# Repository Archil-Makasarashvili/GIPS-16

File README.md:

# GIPS-16
GIPS-16-1 Soviet  plasma display controller

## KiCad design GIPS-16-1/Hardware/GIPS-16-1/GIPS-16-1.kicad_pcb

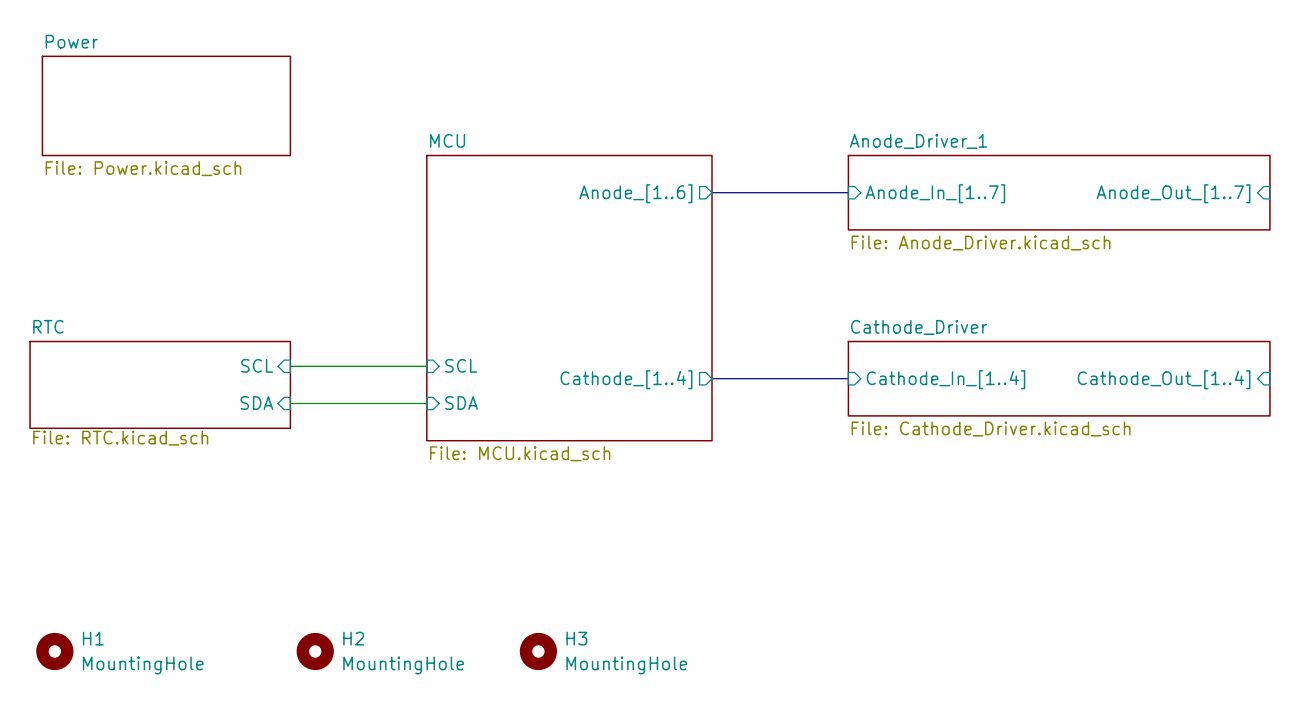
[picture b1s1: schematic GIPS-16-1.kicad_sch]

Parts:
H1, H2, H3: MountingHole; MountingHole_3.2mm_M3

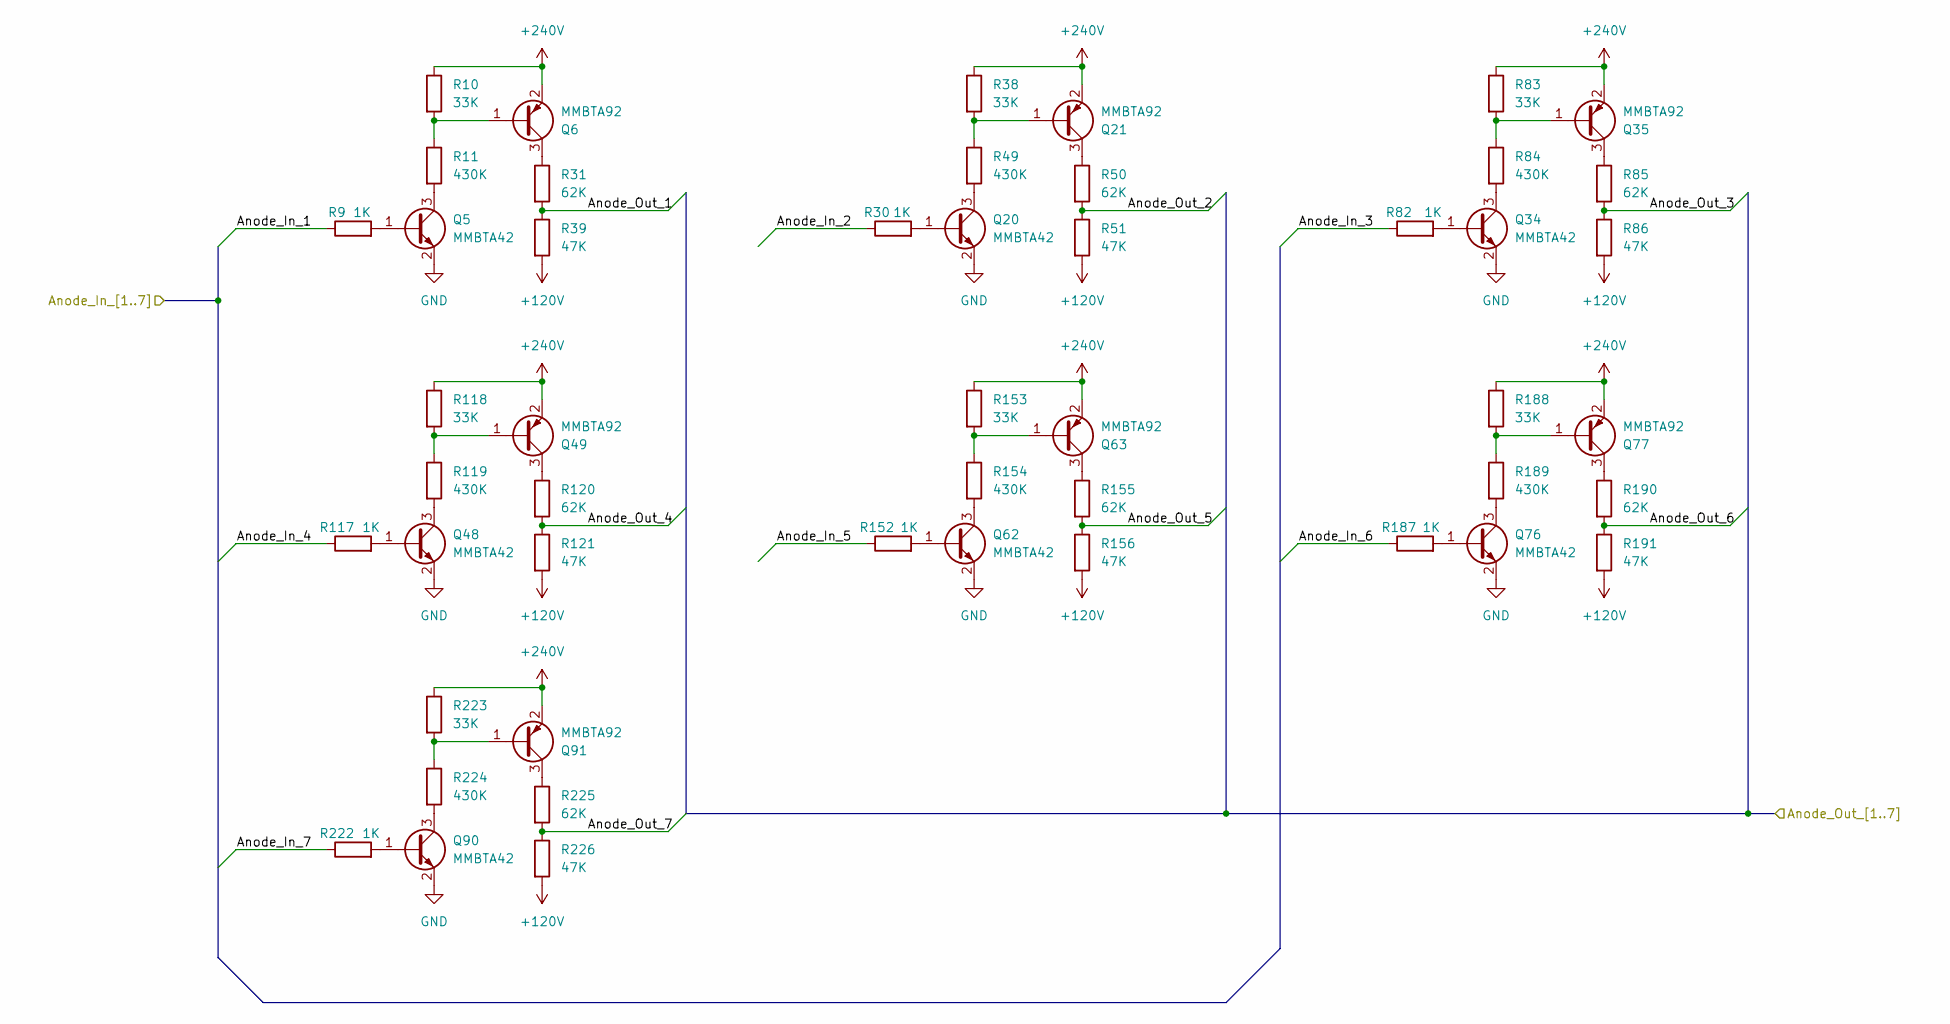
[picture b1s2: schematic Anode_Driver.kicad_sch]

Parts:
Q5, Q20, Q34, Q48, Q62, Q76, Q90: MMBTA42; SOT-23
Q6, Q21, Q35, Q49, Q63, Q77, Q91: MMBTA92; SOT-23
R9, R30, R82, R117, R152, R187, R222: 1K; R_0805_2012Metric_Pad1.20x1.40mm_HandSolder
R10, R38, R83, R118, R153, R188, R223: 33K; R_1206_3216Metric_Pad1.30x1.75mm_HandSolder
R11, R49, R84, R119, R154, R189, R224: 430K; R_1206_3216Metric_Pad1.30x1.75mm_HandSolder
R31, R50, R85, R120, R155, R190, R225: 62K; R_1206_3216Metric_Pad1.30x1.75mm_HandSolder
R39, R51, R86, R121, R156, R191, R226: 47K; R_1206_3216Metric_Pad1.30x1.75mm_HandSolder

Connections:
+120V: R39.2, R51.2, R86.2, R121.2, R156.2, R191.2, R226.2; also elsewhere on the board
+240V: Q6.2 (E), Q21.2 (E), Q35.2 (E), Q49.2 (E), Q63.2 (E), Q77.2 (E), Q91.2 (E), R10.1, R38.1, R83.1, R118.1, R153.1, R188.1, R223.1; also elsewhere on the board
/Anode_Driver_1/Anode_In_1: R9.1; also elsewhere on the board
/Anode_Driver_1/Anode_In_2: R30.1; also elsewhere on the board
/Anode_Driver_1/Anode_In_3: R82.1; also elsewhere on the board
/Anode_Driver_1/Anode_In_4: R117.1; also elsewhere on the board
/Anode_Driver_1/Anode_In_5: R152.1; also elsewhere on the board
/Anode_Driver_1/Anode_In_6: R187.1; also elsewhere on the board
/Anode_Driver_1/Anode_In_7: R222.1
/Anode_Driver_1/Anode_Out_1: R31.2, R39.1
/Anode_Driver_1/Anode_Out_2: R50.2, R51.1
/Anode_Driver_1/Anode_Out_3: R85.2, R86.1
/Anode_Driver_1/Anode_Out_4: R120.2, R121.1
/Anode_Driver_1/Anode_Out_5: R155.2, R156.1
/Anode_Driver_1/Anode_Out_6: R190.2, R191.1
/Anode_Driver_1/Anode_Out_7: R225.2, R226.1
GND: Q5.2 (E), Q20.2 (E), Q34.2 (E), Q48.2 (E), Q62.2 (E), Q76.2 (E), Q90.2 (E); also elsewhere on the board
unnamed: Q5.1 (B), R9.2
unnamed: Q5.3 (C), R11.2
unnamed: Q6.1 (B), R10.2, R11.1
unnamed: Q6.3 (C), R31.1
unnamed: Q20.1 (B), R30.2
unnamed: Q20.3 (C), R49.2
unnamed: Q21.1 (B), R38.2, R49.1
unnamed: Q21.3 (C), R50.1
unnamed: Q34.1 (B), R82.2
unnamed: Q34.3 (C), R84.2
unnamed: Q35.1 (B), R83.2, R84.1
unnamed: Q35.3 (C), R85.1
unnamed: Q48.1 (B), R117.2
unnamed: Q48.3 (C), R119.2
unnamed: Q49.1 (B), R118.2, R119.1
unnamed: Q49.3 (C), R120.1
unnamed: Q62.1 (B), R152.2
unnamed: Q62.3 (C), R154.2
unnamed: Q63.1 (B), R153.2, R154.1
unnamed: Q63.3 (C), R155.1
unnamed: Q76.1 (B), R187.2
unnamed: Q76.3 (C), R189.2
unnamed: Q77.1 (B), R188.2, R189.1
unnamed: Q77.3 (C), R190.1
unnamed: Q90.1 (B), R222.2
unnamed: Q90.3 (C), R224.2
unnamed: Q91.1 (B), R223.2, R224.1
unnamed: Q91.3 (C), R225.1

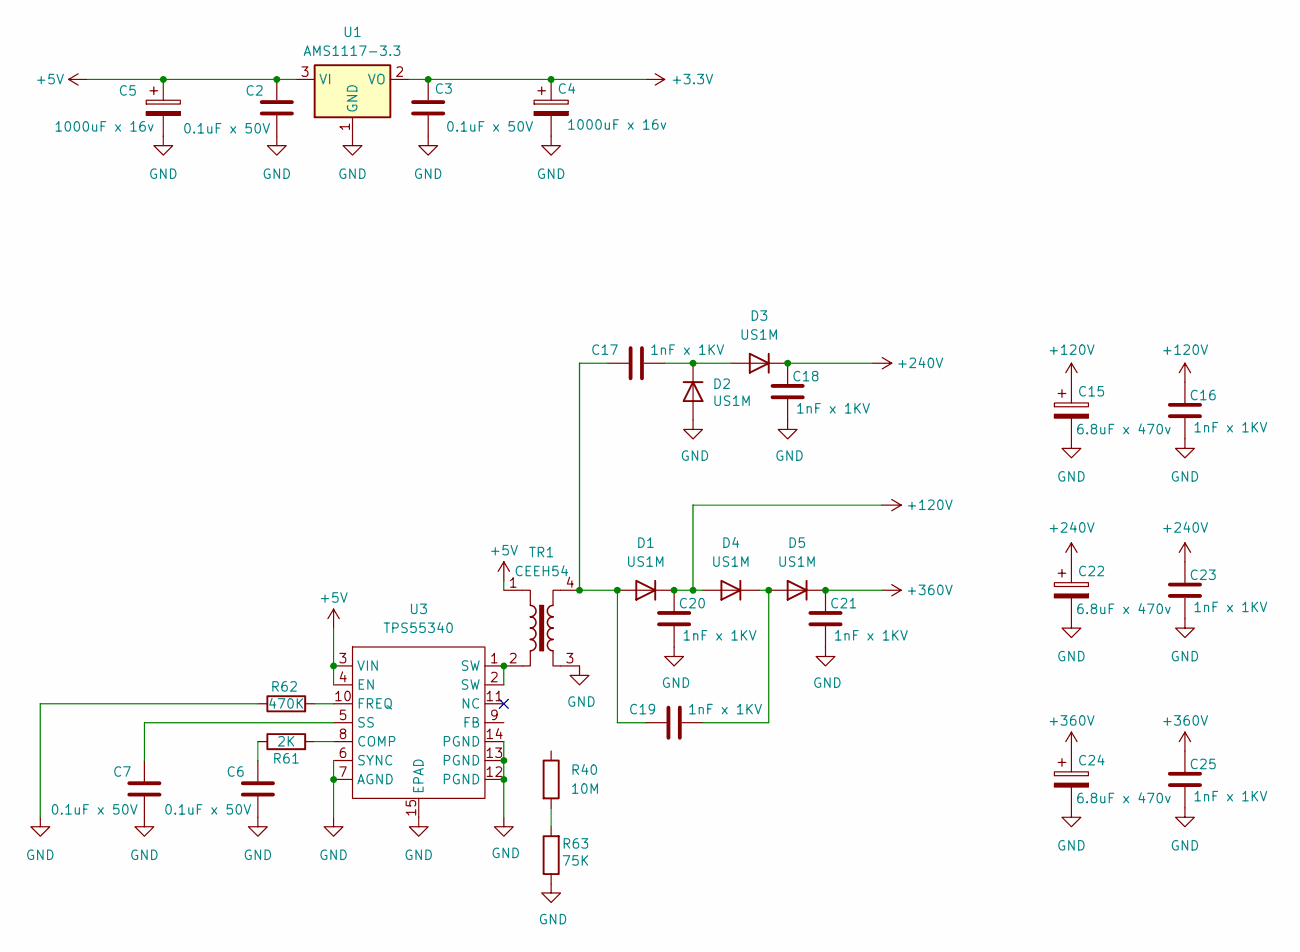
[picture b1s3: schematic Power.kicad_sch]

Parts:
C2, C3, C6, C7: 0.1uF x 50V; C_0805_2012Metric_Pad1.18x1.45mm_HandSolder
C4, C5: 1000uF x 16v; CP_Elec_10x10.5
C15, C22, C24: 6.8uF x 470v; CP_Elec_10x10.5
C16, C23, C25: 1nF x 1KV; C_2220_5750Metric_Pad1.97x5.40mm_HandSolder
C17, C18, C19, C20, C21: 1nF x 1KV; C_Disc_D10.0mm_W2.5mm_P5.00mm
D1, D2, D3, D4, D5: US1M; D_SMA
R40: 10M; R_1206_3216Metric_Pad1.30x1.75mm_HandSolder
R61: 2K; R_0805_2012Metric_Pad1.20x1.40mm_HandSolder
R62: 470K; R_0805_2012Metric_Pad1.20x1.40mm_HandSolder
R63: 75K; R_0805_2012Metric_Pad1.20x1.40mm_HandSolder
TR1: CEEH54; Pulse_P0926NL
U1: AMS1117-3.3; SOT-223-3_TabPin2
U3: TPS55340; TSSOP-14-1EP_4.4x5mm_P0.65mm

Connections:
+3.3V: C3.1, C4.1, U1.2 (VO); also elsewhere on the board
+5V: C2.1, C5.1, TR1.1, U1.3 (VI), U3.3 (VIN), U3.4 (EN); also elsewhere on the board
+120V: C15.1, C16.1, C20.1, D1.1 (K), D4.2 (A); also elsewhere on the board
+240V: C18.1, C22.1, C23.1, D3.1 (K); also elsewhere on the board
+360V: C21.1, C24.1, C25.1, D5.1 (K)
GND: C2.2, C3.2, C4.2, C5.2, C6.2, C7.2, C15.2, C16.2, C18.2, C20.2, C21.2, C22.2, C23.2, C24.2, C25.2, D2.2 (A), R62.1, R63.1, TR1.3, U1.1 (GND), U3.6 (SYNC), U3.7 (AGND), U3.12 (PGND), U3.13 (PGND), U3.14 (PGND), U3.15 (EPAD); also elsewhere on the board
unnamed: C6.1, R61.1
unnamed: C17.1, C19.1, D1.2 (A), TR1.4
unnamed: C17.2, D2.1 (K), D3.2 (A)
unnamed: C19.2, D4.1 (K), D5.2 (A)
unnamed: R40.2, R63.2
unnamed: TR1.2, U3.1 (SW), U3.2 (SW)
unnamed: R61.2, U3.8 (COMP)
unnamed: R62.2, U3.10 (FREQ)
unnamed: C7.1, U3.5 (SS)

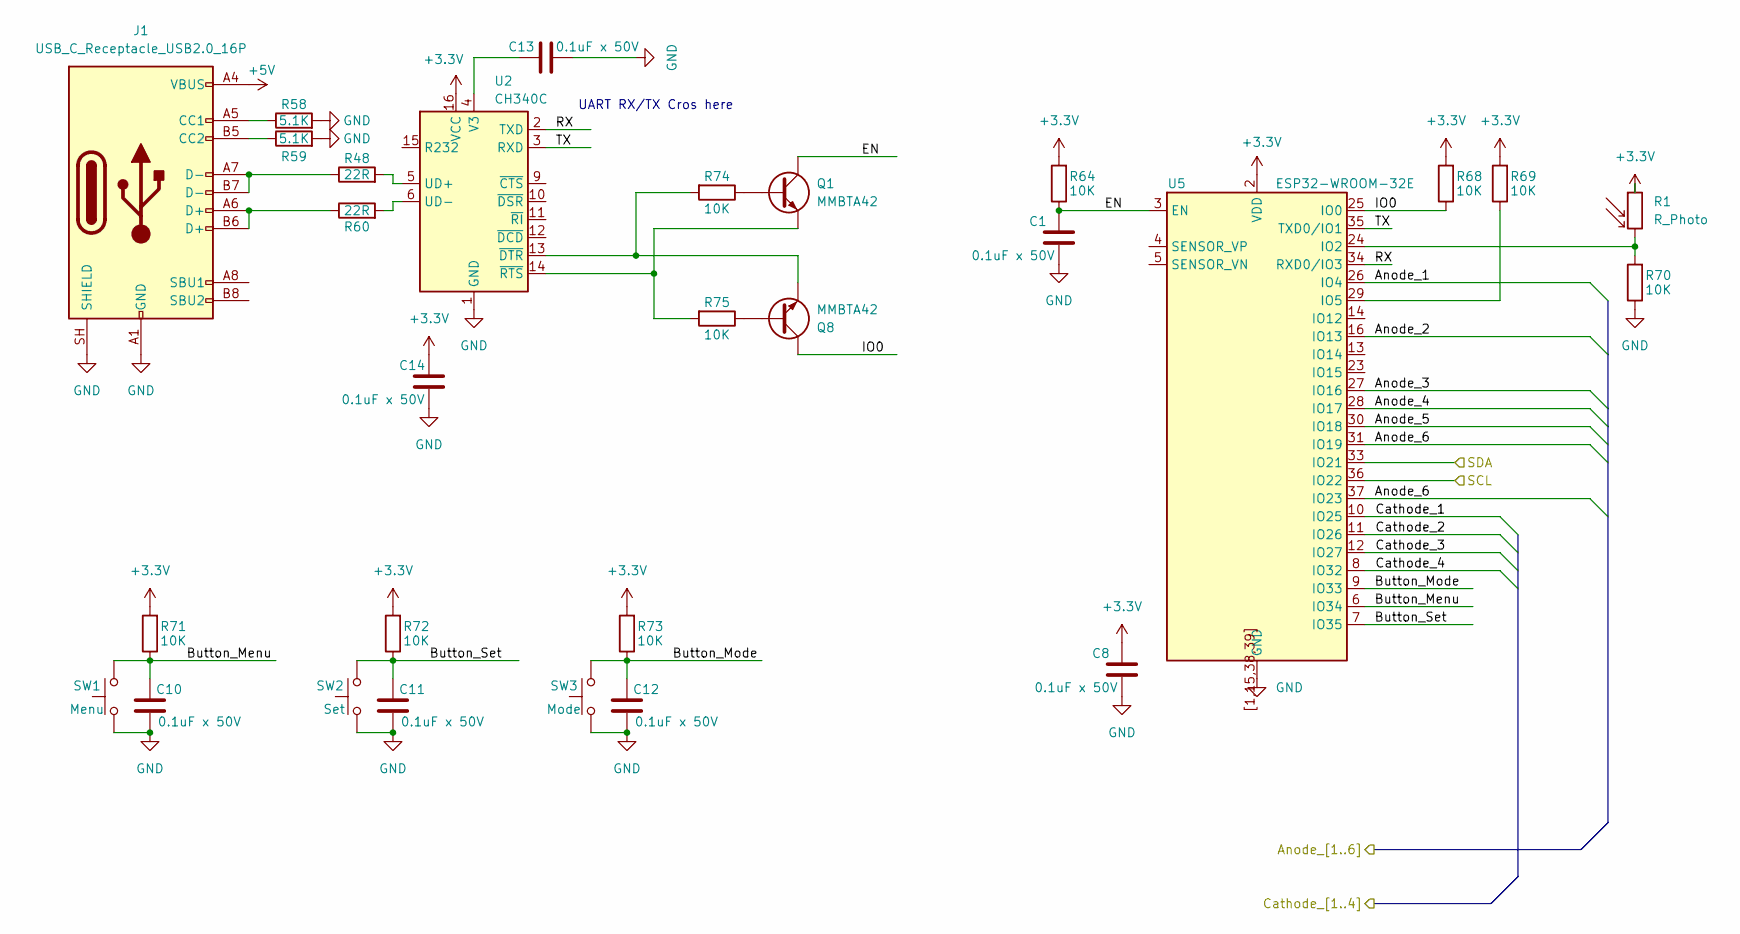
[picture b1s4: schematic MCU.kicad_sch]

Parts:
C1, C8, C10, C11, C12, C13, C14: 0.1uF x 50V; C_0805_2012Metric_Pad1.18x1.45mm_HandSolder
J1: USB_C_Receptacle_USB2.0_16P; USB_C_Receptacle_G-Switch_GT-USB-7010ASV
Q1, Q8: MMBTA42; SOT-23
R1: R_Photo; R_LDR_5.1x4.3mm_P3.4mm_Vertical
R48, R60: 22R; R_0805_2012Metric_Pad1.20x1.40mm_HandSolder
R58, R59: 5.1K; R_0805_2012Metric_Pad1.20x1.40mm_HandSolder
R64, R68, R69, R70, R71, R72, R73, R74, R75: 10K; R_0805_2012Metric_Pad1.20x1.40mm_HandSolder
SW1: Menu; SW_PUSH_6mm_H5mm
SW2: Set; SW_PUSH_6mm_H5mm
SW3: Mode; SW_PUSH_6mm_H5mm
U2: CH340C; SOIC-16_3.9x9.9mm_P1.27mm
U5: ESP32-WROOM-32E

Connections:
+3.3V: C8.1, C14.1, R1.1, R64.2, R68.2, R69.2, R71.2, R72.2, R73.2, U2.16 (VCC), U5.2 (VDD); also elsewhere on the board
+5V: J1.A4 (VBUS), J1.A9 (VBUS), J1.B4 (VBUS), J1.B9 (VBUS); also elsewhere on the board
/Anode_Driver_1/Anode_In_1: U5.26 (IO4); also elsewhere on the board
/Anode_Driver_1/Anode_In_2: U5.16 (IO13); also elsewhere on the board
/Anode_Driver_1/Anode_In_3: U5.27 (IO16); also elsewhere on the board
/Anode_Driver_1/Anode_In_4: U5.28 (IO17); also elsewhere on the board
/Anode_Driver_1/Anode_In_5: U5.30 (IO18); also elsewhere on the board
/Anode_Driver_1/Anode_In_6: U5.31 (IO19), U5.37 (IO23); also elsewhere on the board
/Cathode_Driver/Cathode_In_1: U5.10 (IO25); also elsewhere on the board
/Cathode_Driver/Cathode_In_2: U5.11 (IO26); also elsewhere on the board
/Cathode_Driver/Cathode_In_3: U5.12 (IO27); also elsewhere on the board
/Cathode_Driver/Cathode_In_4: U5.8 (IO32); also elsewhere on the board
/MCU/Button_Menu: C10.1, R71.1, SW1.2, U5.6 (IO34)
/MCU/Button_Mode: C12.1, R73.1, SW3.2, U5.9 (IO33)
/MCU/Button_Set: C11.1, R72.1, SW2.2, U5.7 (IO35)
/MCU/EN: C1.1, Q1.3 (C), R64.1, U5.3 (EN)
/MCU/IO0: Q8.3 (C), R68.1, U5.25 (IO0)
/MCU/RX: U2.2 (TXD), U5.34 (RXD0/IO3)
/MCU/TX: U2.3 (RXD), U5.35 (TXD0/IO1)
/RTC/SCL: U5.36 (IO22); also elsewhere on the board
/RTC/SDA: U5.33 (IO21); also elsewhere on the board
GND: C1.2, C8.2, C10.2, C11.2, C12.2, C13.2, C14.2, J1.A1 (GND), J1.A12 (GND), J1.B1 (GND), J1.B12 (GND), J1.SH (SHIELD), R58.2, R59.2, R70.1, SW1.1, SW2.1, SW3.1, U2.1 (GND), U5.1 (GND), U5.15 (GND), U5.38 (GND), U5.39 (GND), U5.[1,15,38,39] (GND); also elsewhere on the board
unnamed: J1.A5 (CC1), R58.1
unnamed: J1.B5 (CC2), R59.1
unnamed: J1.A6 (D+), J1.B6 (D+), R60.1
unnamed: J1.A7 (D-), J1.B7 (D-), R48.1
unnamed: Q1.1 (B), R74.1
unnamed: Q1.2 (E), R75.2, U2.14 (~RTS)
unnamed: Q8.1 (B), R75.1
unnamed: Q8.2 (E), R74.2, U2.13 (~DTR)
unnamed: R48.2, U2.5 (UD+)
unnamed: R60.2, U2.6 (UD-)
unnamed: C13.1, U2.4 (V3)
unnamed: R1.2, R70.2, U5.24 (IO2)
unnamed: R69.1, U5.29 (IO5)

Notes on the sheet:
UART RX/TX Cros here

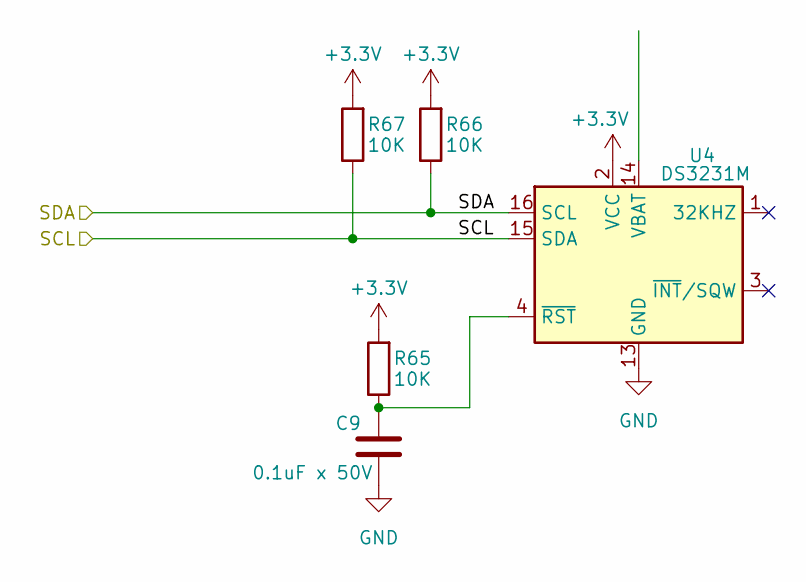
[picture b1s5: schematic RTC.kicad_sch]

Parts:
C9: 0.1uF x 50V; C_0805_2012Metric_Pad1.18x1.45mm_HandSolder
R65, R66, R67: 10K; R_0805_2012Metric_Pad1.20x1.40mm_HandSolder
U4: DS3231M; SOIC-16W_7.5x10.3mm_P1.27mm

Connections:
+3.3V: R65.2, R66.2, R67.2, U4.2 (VCC); also elsewhere on the board
/RTC/SCL: R67.1, U4.15 (SDA); also elsewhere on the board
/RTC/SDA: R66.1, U4.16 (SCL); also elsewhere on the board
GND: C9.2, U4.5 (GND), U4.6 (GND), U4.7 (GND), U4.8 (GND), U4.9 (GND), U4.10 (GND), U4.11 (GND), U4.12 (GND), U4.13 (GND); also elsewhere on the board
unnamed: C9.1, R65.1, U4.4 (~RST)

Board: 2 copper layers, 127 parts (0 on the bottom side), 91 nets, no tracks yet.

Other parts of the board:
Q2, Q3, Q4, Q7: MMBTA42; SOT-23
R2, R4, R6, R8: 1K; R_0805_2012Metric_Pad1.20x1.40mm_HandSolder
R3, R5, R7, R12: 220K; R_1206_3216Metric_Pad1.30x1.75mm_HandSolder

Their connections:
+120V: R3.1, R5.1, R7.1, R12.1; also elsewhere on the board
/Cathode_Driver/Cathode_In_1: R2.1; also elsewhere on the board
/Cathode_Driver/Cathode_In_2: R4.1; also elsewhere on the board
/Cathode_Driver/Cathode_In_3: R6.1; also elsewhere on the board
/Cathode_Driver/Cathode_In_4: R8.1; also elsewhere on the board
/Cathode_Driver/Cathode_Out_1: Q2.3 (C), R3.2
/Cathode_Driver/Cathode_Out_2: Q3.3 (C), R5.2
/Cathode_Driver/Cathode_Out_3: Q4.3 (C), R7.2
/Cathode_Driver/Cathode_Out_4: Q7.3 (C), R12.2
GND: Q2.2 (E), Q3.2 (E), Q4.2 (E), Q7.2 (E); also elsewhere on the board
unnamed: Q2.1 (B), R2.2
unnamed: Q3.1 (B), R4.2
unnamed: Q4.1 (B), R6.2
unnamed: Q7.1 (B), R8.2

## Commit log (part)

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2026-06-10 Add files via upload
    Initial commit.
2026-06-10 Updated directory structure.
